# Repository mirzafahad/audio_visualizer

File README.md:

# RGB LED Backlight and Audio Visualizer

:star: Star me on GitHub — it helps!

A simple WS2812 LED Strip based backlight and audio visualizer using [Adafruit nrf52832 Feather](https://www.adafruit.com/product/3406). You can control the color and modes using an Android App. 

More can be found [here](https://mirzafahad.github.io/2020-07-13-audio-visualizer/).

Backlight in action:  

Motion Detection:  

Android App:  

Hardware:

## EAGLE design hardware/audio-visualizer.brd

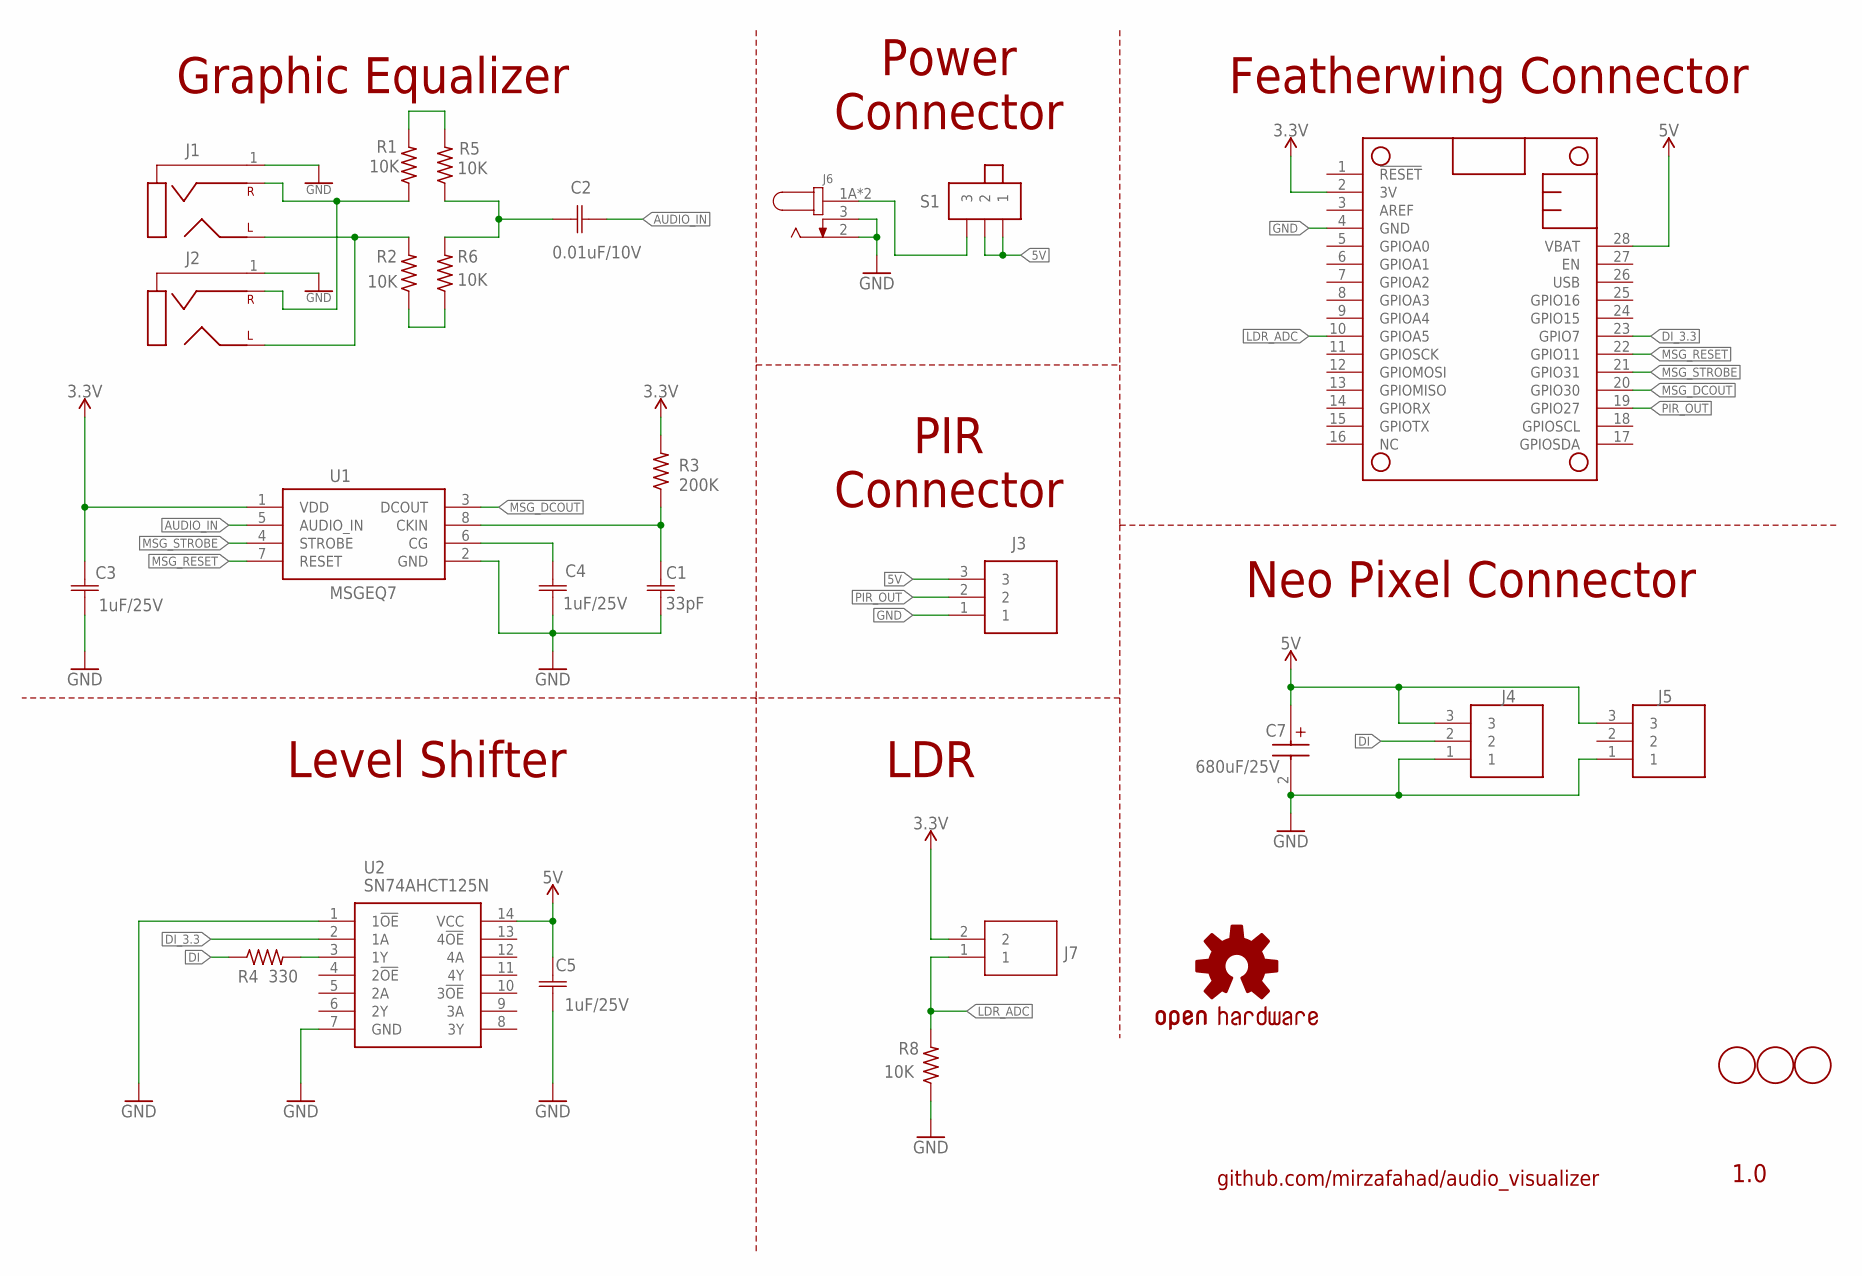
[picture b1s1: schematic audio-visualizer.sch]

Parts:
C1: 33pF; CAP_CL21_SAM
C2: 0.01uF/10V; CAP_CL21_SAM
C3, C4, C5: 1uF/25V; CAP_CL21_SAM
C7: 680uF/25V; CAPAE830X1050N
J1, J2: SJ-3523-SMT-TR; SJ3523SMTTR
J3, J4, J5: 0022057035
J6: PJ-002AH-SMT-TR; CUI_PJ-002AH-SMT-TR
J7: 22-05-7025; MOLEX_22-05-7025
LOGO1: OSHW-LOGOL-COPPER; OSHW-LOGO-L_COPPER
MS1: FEATHERWING_JUST_PINS
R1, R2, R5, R6, R8: 10K; R0805
R3: 200K; R0805
R4: 330; R0805
S1: JS102011SAQN
U1: MSGEQ7P; DIP08
U2: SN74AHCT125N; DIP794W53P254L1930H508Q14N
U$2, U$3, U$4: FIDUCIAL; FIDUCIAL_1MM

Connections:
3.3V: C3.1, J7.2, MS1.2 (3V), R3.2, U1.1 (VDD)
5V: C5.1, C7.1 (+), J3.3, J4.3, J5.3, MS1.28 (VBAT), S1.1, S1.2, U2.14 (VCC)
AUDIO_IN: C2.2, U1.5 (AUDIO_IN)
DI: J4.2, R4.1
DI_3.3: MS1.23 (GPIO7), U2.2 (1A)
GND: C1.2, C3.2, C4.2, C5.2, C7.2 (-), J1.1, J2.1, J3.1, J4.1, J5.1, J6.2, J6.3, MS1.4 (GND), R8.1, U1.2 (GND), U2.7 (GND)
LDR_ADC: J7.1, MS1.10 (GPIOA5), R8.2
MSG_DCOUT: MS1.20 (GPIO30), U1.3 (DCOUT)
MSG_RESET: MS1.22 (GPIO11), U1.7 (RESET)
MSG_STROBE: MS1.21 (GPIO31), U1.4 (STROBE)
unnamed: R1.2, R5.2
unnamed: R2.1, R6.1
unnamed: C2.1, R5.1, R6.2
unnamed: C1.1, R3.1, U1.8 (CKIN)
unnamed: C4.1, U1.6 (CG)
unnamed: J1.2 (5), J2.2 (5), R2.2
unnamed: R4.2, U2.3 (1Y)
unnamed: J1.3 (2), J2.3 (2), R1.1
unnamed: J6.1A (1), J6.1B (1), S1.3
PIR_OUT: J3.2, MS1.19 (GPIO27)

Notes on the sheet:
Graphic Equalizer
Featherwing Connector
Neo Pixel Connector
Level Shifter
Power Connector
LDR
PIR Connector
1.0
github.com/mirzafahad/audio_visualizer

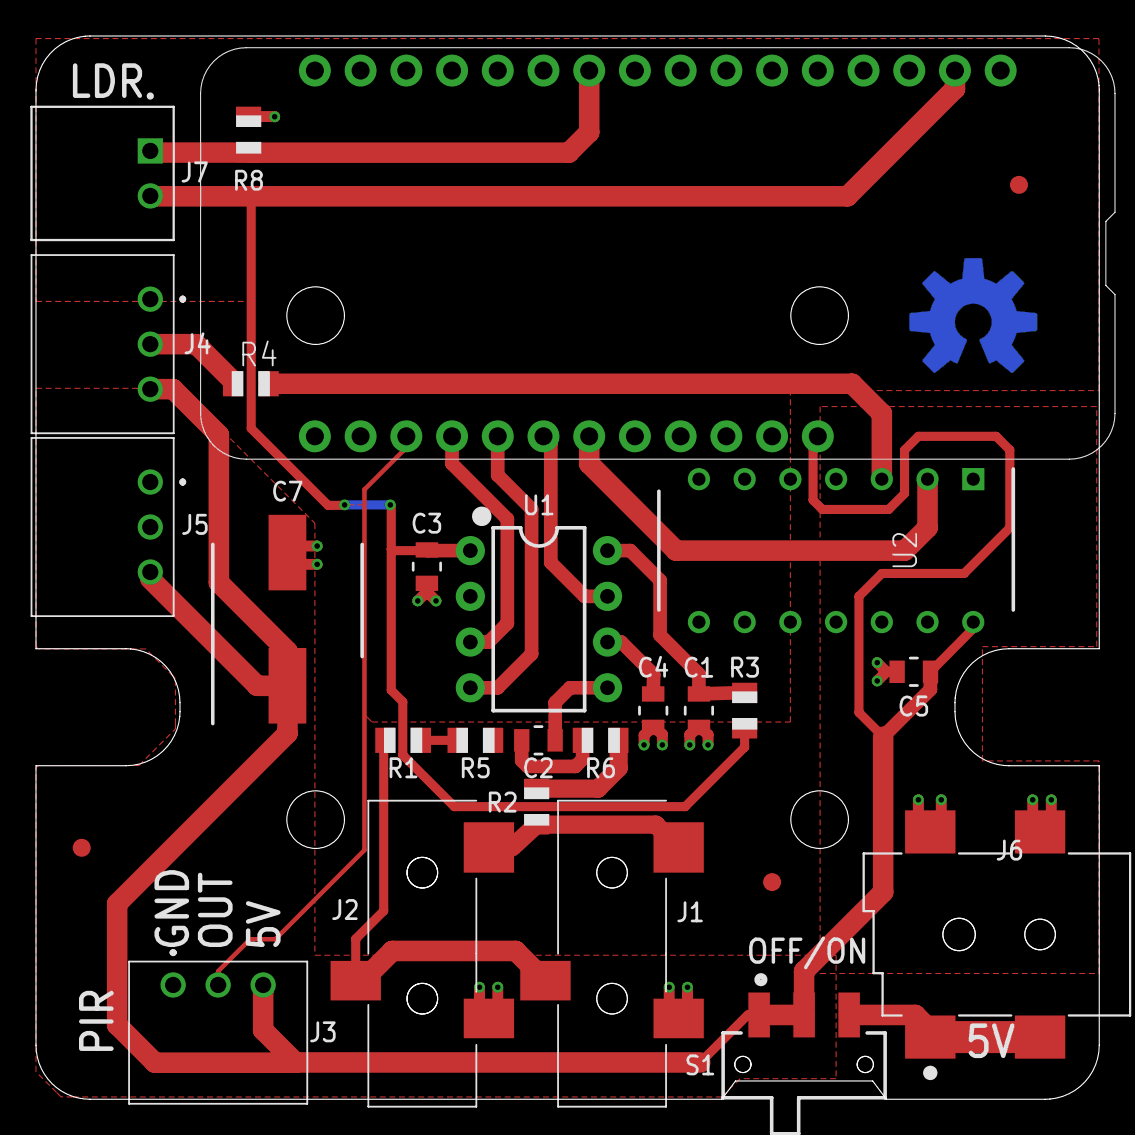
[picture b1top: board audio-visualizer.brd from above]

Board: 2 copper layers, 59.1 x 59.1 mm, 28 parts (1 on the bottom side), 20 nets.

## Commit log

2019-12-25 Initial commit. Audio visulization is working;
2020-01-07 Settled with just 4 freq instead of all 7 freq;
2020-05-02 Minor changes;
2020-07-10 Cleanup;
2020-07-10 Command types are added;
2020-07-10 Added Bluetooth Initializtion.
2020-07-11 Separate files for bluetooth. Finished the project.
2020-07-18 Updated readme. Added comments in the code.
2020-07-18 Updated image position on readme.
2020-07-18 Updated file name.
2020-07-18 Spelling mistake.
2020-08-13 Added schematic.
2020-08-13 pdf schematic added.
2020-10-20 tv code added;
2020-10-20 Made some changes to threshold.
2020-10-20 Updated folder structures.
2020-10-21 Cleanup.
2020-10-21 Added Android code and apk file.
2020-10-21 Schematic PDF is added.
2020-10-31 Updated readme, Default light set to white.
2020-11-28 Updated read me.
2020-11-28 Updated readme.
2020-11-30 Added a debug msg and updated the Serial baudrate.
2021-06-02 Now the backlight turns ON when the TV is turned ON and turns OFF when the TV is turned OFF. When the TV is turned ON the USB ports of the TV gets power. That is fed to an ADC after a voltage divider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
2021-06-02 Incresed the LED numbers to cover more area. Not doing audio spectrum for the TV backlight. During dark times (!) the light will stay on for longer (30s to 1min). Changed the default color to Blue fr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

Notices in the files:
README.md:
License: MIT
parts and their libraries:
SparkFun-Aesthetics: Licensing: Creative Commons ShareAlike 4.0 International - https://creativecommons.org/licenses/by-sa/4.0
COPYRIGHT: Copyright (C) 2018 Accelerated Designs. All rights reserved
